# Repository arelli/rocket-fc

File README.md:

# rocket-fc

Open-source flight computer and ground station for model rockets, built on
the **Seeed XIAO ESP32-S3 + Wio-SX1262** (LoRa) kit.

The flight computer detects launch and apogee, fires the parachute ejection
charge, logs the flight to its own flash and sends live telemetry. A second
kit is the ground station: it receives the telemetry, serves the whole
control page over its own WiFi to a phone or laptop, and can be the launch
controller for the motor igniter.

> **Status:** version 0.1, bench-tested, not yet flown. Read
> [Safety](#safety) before building.

## Features

**Flight computer**
- Launch, burnout, apogee and landing detection (Kalman filter on barometer
  + accelerometer); single-shot ejection with lockout, confirmation and
  minimum altitude; optional deployment delay and backup timer.
- Layered pyro safety: hardware arm link, gate pull-down, software interlock
  until launch is detected, one shot per flight even across resets.
- Resumes a flight after an in-flight processor reset.
- Flight log in the XIAO's flash (4.8 MB, sessions kept after power-off) and
  PSRAM; no SD card needed.
- LoRa telemetry with CRC, duty-cycle limiter (EU 869 MHz by default) and
  event priority; attitude estimate; optional L76K GPS for recovery.
- LED and buzzer codes for every state, self-test faults and the landed
  altitude.

**Ground station**
- WiFi access point serving the UI: live gauges, attitude, plots, events,
  GPS recovery bearing, battery, both kits' settings and consoles, onboard
  log download. No app, no internet, no laptop needed.
- Launch controller: ARM switch, igniter continuity, countdown, abort.
- BENCH / FLIGHT mode switch the rocket follows; ping and signal-search mode;
  manual ejection by radio (optional, off by default).
- Every panel part (switches, button, buzzer, LEDs, battery) is optional.

**Software**
- Every tunable value is a setting: stored in flash, edited from the UI,
  identified by a CRC that is logged with the firmware commit.
- Decision logic is hardware-independent and unit-tested on the PC (17 test
  suites, including complete simulated flights).

## Hardware

| Kit | Parts |
|---|---|
| Flight computer | XIAO ESP32-S3 + Wio-SX1262, MPU-9250 IMU, BMP280 barometer, IRLB8748 pyro MOSFET, buzzer, LED, 18350 Li-ion cell, optional L76K GPS |
| Ground station | XIAO ESP32-S3 + Wio-SX1262, 18650 Li-ion cell (or a power bank), optional ARM / MODE switches, push button, launch MOSFET, buzzer, two LEDs |

| Flight computer | Ground station |
|---|---|
|  |  |

Full parts list, assembly and first-time setup:
**[docs/BUILD.md](docs/BUILD.md)**.

### PCBs

KiCad 10 boards for a home-made build (laser and etch), each part tagged on
the 3D render with what goes into each screw terminal and the resistor colour
codes.

**Flight computer** ([hardware/flight-pcb](hardware/flight-pcb/README.md)):

**Ground station** ([hardware/ground-pcb](hardware/ground-pcb/README.md)):

## Quick start

1. Build the two kits ([docs/BUILD.md](docs/BUILD.md)).
2. Install [VS Code](https://code.visualstudio.com/) with the **PlatformIO
   IDE** extension, clone this repository and open it.
3. Flash each kit over USB-C:
   ```
   pio run -e flight -t upload     # flight computer
   pio run -e ground -t upload     # ground station
   ```
4. Join the station's WiFi `rocketfc-XXXX` (password: `wifi` on its USB
   console the first time) and open **http://192.168.4.1**.
5. Set your own pairing key `rf_key`, press **Set upright**, and work
   through [docs/TESTING.md](docs/TESTING.md).

| PlatformIO env | Builds |
|---|---|
| `flight` | Flight computer firmware. One firmware for bench and flight: the test commands (simulated flight, test fire) need **bench mode**, which follows the ground station's MODE and ends at launch. |
| `ground` | Ground station firmware, with the UI embedded. |
| `native` | Unit tests on your computer: `pio test -e native` (needs a C++ compiler). |

## Safety

This project drives pyrotechnic charges and motor igniters.

- Run the whole bench procedure in [docs/TESTING.md](docs/TESTING.md) with a
  dummy load and bare nichrome **before fitting any charge**.
- Fit arm links and connect igniters last, at the pad, from the side.
- Read [docs/FLIGHT_LOGIC.md](docs/FLIGHT_LOGIC.md) to know exactly when the
  charge can fire.
- Set your own `rf_key` (the default is public) and keep the station's WiFi
  password private: anyone on that WiFi has the launch and ejection controls.
- Fly under your club's and your country's rules, including the radio rules
  for the band you use.

The software is provided as is, without warranty (see [LICENSE](LICENSE)).

## Documentation

| Document | Contents |
|---|---|
| [BUILD.md](docs/BUILD.md) | Parts, wiring, flashing, first-time setup, troubleshooting |
| [HARDWARE.md](docs/HARDWARE.md) | Pin maps, power, pyro and launch circuits, ground station panel, WiFi |
| [TESTING.md](docs/TESTING.md) | Unit tests, bench tests, pre-flight checklist |
| [FLIGHT_LOGIC.md](docs/FLIGHT_LOGIC.md) | States, deployment rules, interlocks, failure handling |
| [SETTINGS.md](docs/SETTINGS.md) | Every setting, how to change them, radio rules, bench mode |
| [INDICATORS.md](docs/INDICATORS.md) | LED patterns and buzzer codes |
| [TELEMETRY.md](docs/TELEMETRY.md) | Radio protocol, frame formats, CSV columns, logs |
| [ARCHITECTURE.md](docs/ARCHITECTURE.md) | Code structure, data flow, how to extend |

## Repository layout

```
include/        pin map (board_pins.h) and fixed constants
lib/fc_core/    hardware-independent logic, unit-tested on the PC
                (state machine, estimator, telemetry, settings, flash log, GPS,
                 launch control, remote-command codes, ...)
lib/fc_hal/     drivers: MPU-9250, BMP280, SX1262, GPS UART, flash, pyro, ADC, system
src/flight/     flight computer firmware (wiring of core + drivers)
src/ground/     ground station firmware and its WiFi server
test/           unit tests (pio test -e native)
tools/          ground_station.html (the UI), ground_station.py (USB recorder),
                pcb_export.py (KiCad checks and exports; with
                pcb_check.py, pcb_map.py, pcb_isolation.py, pcb_parts.py),
                schematics.py (ground station drawing), build scripts
hardware/       flight-pcb: KiCad 10 project of the flight computer
                (schematic = wiring master; routed board, laser files
                for a home-made build); ground-pcb: the ground station
                on a single-sided board
docs/           documentation and schematics
```

## Traceability

Every build is stamped with its git commit (`-dirty` if there were
uncommitted changes), printed at boot and logged as the first telemetry
event. The settings in use are identified by a CRC-32 (boot banner,
`status`, CONFIG event). Fly clean builds and keep the exported settings
file: a log then identifies exactly which code and configuration flew.

## Contributing

Bug reports, flight reports, hardware variants and code are welcome. See
[CONTRIBUTING.md](CONTRIBUTING.md) and the
[code of conduct](CODE_OF_CONDUCT.md). Changes are listed in
[CHANGELOG.md](CHANGELOG.md).

## License

[MIT](LICENSE).

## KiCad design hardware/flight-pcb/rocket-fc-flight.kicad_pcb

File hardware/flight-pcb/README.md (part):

# Flight computer PCB (KiCad 10)

KiCad project of the flight computer. The schematic is the **wiring master**:
pin numbers follow [include/board_pins.h](../../include/board_pins.h), and
[docs/HARDWARE.md](../../docs/HARDWARE.md) explains each circuit.

| File | Contents |
|---|---|
| `rocket-fc-flight.kicad_pro` | Project, design rules and net classes |
| `rocket-fc-flight.kicad_sch` | Schematic (one A3 sheet) |
| `rocket-fc-flight.kicad_pcb` | Board: 30 x 68 mm (75 mm with the mounting ears), two layers |
| `lib/rocket-fc.kicad_sym` | Symbols: XIAO ESP32-S3 + Wio-SX1262, SparkFun MPU-9250 breakout, 4-pin GY-BMP280, L76K |
| `lib/rocket-fc.pretty/` | Footprints of those modules, and the wire pads of J1 and J3 |
| `lib/rocket-fc.3dshapes/` | Simplified 3D models of those (boxes and cylinders, for the renders and the tube check by eye) |
| `out/` | Generated files (not committed) |

The library tables use `${KIPRJMOD}`, so the project opens on any computer
with no library setup.

**Status:** schematic done (ERC clean), board routed with a GND pour on
both faces: DRC 0 problems, schematic parity 0, `tools/pcb_check.py` ok.
Laser files ready (below); test etches of the raster method done, the
vector isolation method still to try. Since those etches: the cell, main
switch and arm link are soldered wires (no JST plug, one screw terminal
fewer) and the board is 6.6 mm shorter.

Routing uses both faces and **27 wire vias**: a hole with a short wire
soldered on both sides wherever a track changes face (no plated holes).

## Layout

The board sits centred in the 32 mm airframe, so the tall parts are on the
centre line and only low parts (resistors lying flat) are near the edges.
`y` runs from the XIAO's USB face (0) to the far end (68 mm).

| Zone (y, mm) | Top | Bottom |
|---|---|---|
| −7–0 | Two ears with M3 holes H1, H2; the notch between them is free for the USB-C plug | The cell and main switch wires (J1) leave through the same notch |
| 0–34 | XIAO with the Wio-SX1262 on top, USB-C flush with the notch; continuity divider (R4, R5, C3) on the left edge, battery divider (R1, R2, C2) on the right; BAT+ / BAT− wire pads | J1: four wire pads at y 9.5 (1 cell −, 2 cell +, 3–4 main switch); SparkFun MPU-9250 |
| 25–56 | Buzzer centred (34–46), gate resistors R6, R7 and the GPS lead pads J5 on the right edge | IRLB8748 (left) and 1 Ω 2 W resistor (right) lying flat (32–53); 470 µF standing between them (45–54) |
| 46–61 | 4-pin GY-BMP280, sensor side down, header at its far edge | |
| 56–59 | ARM link wire pads J3, one at each edge beside the barometer: CELL+ left, ARM right (seen from the top) | |
| 60–70 | | Screw terminal J4 (igniter), centred, pins at y 65 just past the barometer's joints; its wire entry overhangs the far end by 1.7 mm |
| 61–68 | M3 holes H3, H4 in the corners | |

- **USB:** the XIAO's USB-C face is at the board edge, in a 14 mm wide notch
  between the two ears, so the plug goes straight in with the board on its
  sled.
- **One connector:** the igniter's screw terminal J4, on the centre line
  (where the tube is tallest), wires entering from the far end. The cell,
  main switch and arm link are **soldered wires** (lighter than plugs and
  terminals, and they cannot shake loose): J1's four pads under the XIAO,
  J3's two pads at the edges beside the barometer. 0.5 mm² (20 AWG) stranded
  wire for J1 and J3 (they carry the firing current); tie or glue each lead
  to the board or sled next to its pad, so it does not flex at the joint.
- **No status LED** (the buzzer stays): see docs/HARDWARE.md.
- The L76K GNSS module is off the board, near the nose, on a 3-wire lead
  soldered to J5 (3V3, GND, TX); its symbol and footprint stay in the library.

| Footprint | Source |
|---|---|
| XIAO + Wio-SX1262 (U1) | XIAO pattern: 2 x 7, 2.54 mm pitch, rows 15.24 mm apart, 21 x 17.8 mm; **5V, D8, D9, D10 have no pad** (pull those pins out of the header strip before soldering it: the radio uses them through its own connector); two wire pads for the BAT pads on the XIAO underside, past the MPU |
| SparkFun MPU-9250 (U2) | SparkFun's Eagle board file, v10 (17.0 x 17.8 mm); chip side away from the board (its labelled side faces the PCB); **AD0, INT, AUXCL, AUXDA have no pad** (pull those pins); its standoff holes are not drilled (they would hit the XIAO pins) |
| GY-BMP280 4-pin (U3) | 10 x 13 mm, 2.54 mm header along a 10 mm edge. **Mounted sensor side down** (labels up, VIN in the square pad): with the sensor up, the real board's pin order (VIN GND SCL SDA) runs the other way to this footprint. The BMP280 then hangs about 1.5 mm above C1's joints |
| C1 470 µF 10 V | KiCad CP_Radial_D8.0mm_P3.50mm, standing on the bottom (12.5 mm tall at most) |
| Everything else | KiCad standard library: resistors lying flat (7.62 mm), 1 Ω 2 W (DIN0414, 15.24 mm), TO-220 lying flat, a 5.08 mm screw terminal (J4), 12 mm buzzer, solder-wire pads for the GPS lead. J1 and J3 are wire pads from `lib/rocket-fc.pretty/` (J1: the JST-XH 4-pin pad layout without the plug, 0.95 mm holes; J3: two separate 1.3 mm pads 20.8 mm apart). The two 100 nF discs sit at the board edge: **bend them flat** (3.5 mm high at most) |

## Parts

Every part tagged on the 3D render, what goes into each screw terminal
and wire pad (yellow tags), each part's value and what it is, and for the resistors the
colour code (4-band 5 %, 5-band 1 %; the render shows the 4-band one). Parts
on both faces: the bottom panel is seen from below. `python
tools/pcb_export.py board` redraws it (`tools/pcb_parts.py`, needs Pillow).

## Dimensions

Both faces straight on with the outline (30 x 68 mm, 75 mm with the ears;
ears 8 mm wide and 7 mm deep beside the 14 mm USB notch) and the M3 hole
positions (22.5 mm across, 67.75 mm along, 3.75 mm from the sides and the far
end, 3.5 mm from the ear tips) for the sled; the 27 wire vias ringed by net;
3D views of both faces. The same sheet with the parts list beside it:
[dims-parts.jpg](dims-parts.jpg):

`python tools/pcb_export.py board` redraws
both (`tools/pcb_dims.py`, needs Pillow).

## Making the board (laser and etch)

Both faces carry a **GND pour**: the copper between the tracks is kept and
tied to GND (0.7 mm from every other net, thermal spokes on GND pads), so
the laser only has to clear a band around each track and pad, and the etch
removes far less copper. Pieces of the pour that reach no GND pad stay as
floating copper (harmless). No pour under Q1's metal tab or the M3 screw
heads (keep-out areas; `tools/pcb_check.py` checks it); the laser files leave
the paint there, so a home-made board has unconnected copper islands under
them, touching no net. The tracks still
make every connection; the pour only adds to the GND ones.

**Ready to use:** [laser/](laser/) holds every file below for the current
board, and [rocket-fc-flight-laser.zip](laser/rocket-fc-flight-laser.zip)
all of them in one download. `python tools/pcb_export.py laser` writes them
to `out/laser/` and copies them there:

| File | Use |
|---|---|
| `…-top-isolation.nc`, `…-bottom-isolation.nc` | **Vector isolation G-code** (method A, below): outlines around all copper, the bottom mirrored |
| `…-top.svg`, `…-top-0.08mm.png` | Top copper as a raster image (method B), **negative**: black = laser fires (paint off, copper etched), white = copper stays. Only a 0.4 mm band round the copper is black, as in method A: areas without copper (the USB notch, under Q1's tab, round the M3 holes and the labels) stay white and end up as unconnected copper islands. Every hole centre is a small black dot, so the etch leaves a pit that centres the drill; the M3 holes and Q1's tab hole get a 0.6 mm black ring round that dot, so they are easy to find |
| `…-bottom.svg`, `…-bottom-0.08mm.png` | Bottom copper, the same, **mirrored** (as seen from below) |
| `…-jig.svg` | Registration jig: two 3 mm pin holes at the H1 and H4 positions |
| `….drl`, `…-drl_map.pdf`, `…-drill-report.txt` | Drill file (mm), drill map and hole count per size |
| `…-placement-map.png` | Where every part goes, both faces as lasered, with the 27 wire vias (red X) and the pins to solder on both faces (red ring, on the part's face): print it for assembly. Needs PyMuPDF (`pip install pymupdf`), like the PNGs |

Every file uses the same frame, the board outline's bounding box (30.0 x
75.0 mm), so they line up when placed at the same position:

- **LaserGRBL:** give every job the **same Offset X / Y** (e.g. 0, 0) and
  never move the bed or the jig between them. The G-code coordinates already
  start at the lower-left corner of that box (X 0–30, Y 0–75), so run it
  with the same origin as the jig. The PNGs come out 30.0 x 75.0 mm from
  their DPI (Autosize on): within half a line of the SVGs.
- **LightBurn:** one project, one layer each, align their centres; set the
  jig's outline to a layer that does not output.

### Method A: vector isolation (recommended, about 30 minutes a face)

`tools/pcb_isolation.py` turns KiCad's copper into outlines for the laser:
rings around all copper, starting half a spot from its edge, 20 % overlap,
until a 0.4 mm band is clear (where two rings meet in a narrow gap the gap
is already clear, and an outline never enters copper). Nothing else is
burned: areas without copper (the keep-outs under Q1's tab and the screw
heads, the gaps the pour leaves round the labels, the USB notch) stay painted
and become unconnected copper islands, harmless since they touch no net;
every hole centre gets a burned dot (the etched pit centres the drill), a
0.6 mm one at the M3 holes and Q1's tab hole; the board outline is traced as a cutting line. It then checks its own result: the copper left must contain all of
the design's copper, and no two nets may end up joined (a run that fails
exits with an error).

Open the `.nc` file in LaserGRBL (*File → Open*) and run it. The power is
M4 (dynamic): with GRBL's laser mode on (`$32=1`) the power drops in the
corners where the head slows down, so they do not over-burn. Settings, as
environment variables for `python tools/pcb_export.py laser`:

| Variable | Default | Meaning |
|---|---|---|
| `LASER_SPOT` | 0.1 | Burned line width (mm): measure a line on the test scrap |
| `LASER_BAND` | 0.4 | Width cleared around the copper (mm) |
| `LASER_FEED` | 300 | Speed (mm/min) |
| `LASER_S` | 980 | Power, of GRBL's `$30` maximum (1000 by default) |

### Method B: raster image (about 70 minutes a face)

The PNGs are for raster software such as LaserGRBL: pure black and white,
one pixel per line, 0.08 mm (12.5 lines/mm, stored in the file as 317.5
dpi). Lines narrower than the spot leave stripes of paint between them, so
the spacing is smaller than a diode laser's spot. Each face gets **two
passes without moving anything** in between:

1. **Horizontal:** load the PNG with **Passthrough** (engraves it exactly
   as it is, one line per pixel row; Autosize from the DPI).
2. **Vertical:** load the same PNG again with **Line To Line Tracing**,
   *Direction: Vertical*, *Quality* 12.5 lines/mm (the file's own
   resolution, so it is not resampled), same size and offset; check in the
   preview that it matches the image. It clears the paint left between the
   horizontal lines and cuts the vertical edges straight (one pass alone
   leaves a sawtooth on the edges across its lines).

Avoid **Vectorize**: it smooths the outlines and thins narrow tracks and pad
rings. For another line spacing set `LASER_LPMM` (lines per mm, e.g.
`LASER_LPMM=10 python tools/pcb_export.py laser` for 0.1 mm) and use the
same value as the vertical pass's Quality.

### Steps

1. **Blank:** double-sided FR4, 1.6 mm, at least 36 x 82 mm. Clean both
   faces (fine abrasive pad, then isopropyl alcohol) and spray thin coats of
   matte black paint on both. **Find the laser settings on a scrap** painted
   the same way first:
   - a power ladder at a fixed speed (e.g. 50, 65, 80, 98 % at 1000 mm/min);
     take the **lowest power that leaves bright copper**: more power burns
     past the edges and thins tracks and pad rings;
   - method A: measure the width of a single burned line and set
     `LASER_SPOT` to it (re-export), so the rings overlap properly;
   - method B: try both passes (horizontal, then vertical); if stripes of
     paint still stay between the lines, re-export with `LASER_LPMM=15`
     (0.067 mm);
   - LaserGRBL laser mode: M4 (dynamic) is better if GRBL's laser mode is on
     (`$32=1`); for the raster, M3 (constant power) also works, since every
     line ends in the margin outside the board.
2. **Top:** laser `top` onto the blank (method A: the `.nc` file; method B:
   both raster passes).
3. **Drill the four M3 holes** (3.2 mm) on their marks: they register the
   second face.
4. **Jig:** fix a sheet of cardboard or MDF to the bed and, without moving
   it afterwards, cut `jig` into it (a vector job: enough power and passes
   to cut through, at the same offset as the copper). Push two 3 mm pins
   into the holes (drill bits shank-down, or M3 screws from below),
   standing no higher than the board.
5. **Bottom:** flip the board **left to right** (about its long axis) onto
   the pins: H2 and H3 now sit on them. Laser `bottom` at the same position
   as the jig.
6. **Etch** both faces (ferric chloride or sodium persulfate), strip the
   paint with acetone. **TOP and BOT must read correctly** on their faces; if
   BOT is mirror-writing, the bottom was not mirrored. Check every track for
   breaks and shorts with a meter before drilling (also each track against
   the GND pour next to it).
7. **Drill** from the etched pits, then cut and file to the outline (the
   thin copper line on each face). Bits:

| Bit | Holes |
|---|---|
| 0.8 mm | 27 wire vias, resistors, 100 nF, C1, GPS lead pads (J5) |
| 1.0 mm | XIAO, MPU-9250 and barometer headers, BAT pads, buzzer, J1 wire pads |
| 1.2 mm | IRLB8748 (Q1) leads, 1 Ω 2 W (R3) |
| 1.3 mm | ARM link wire pads J3, screw terminal J4 |
| 3.2 mm | M3 holes H1–H4 (step 3) |
| 3.5 mm | Q1's tab hole (a 3.2 mm hole also takes the M3 screw) |

## Assembly order

No plated holes: a part is soldered on the face opposite to it, and some
joints end up under a part. `tools/pcb_check.py` lists them, and the
placement map ([laser/rocket-fc-flight-placement-map.png](laser/rocket-fc-flight-placement-map.png)) shows where each part goes,
the wire vias and the both-face pins; in practice:

0. **All 27 wire vias first**: a bare wire (e.g. a resistor lead offcut)
   through each 0.8 mm via hole, soldered on both faces and trimmed flush.
   Several sit under parts (the XIAO, MPU, buzzer, barometer, J4, R3, R4,
   R7).
1. Small parts in the edge strips, then Q1, R3 and C1 (bottom). **Trim C1's
   joints flush** on the top and put Kapton tape over them: the barometer's
   sensor hangs over them.
2. The J1 wires (cell −, cell +, main switch, main switch): in from the
   bottom, soldered on top and **trimmed flush**, under where the XIAO goes.
   Strip about 3 mm, so no bare wire shows on the bottom.
3. The XIAO's header strips (top, **low male headers, not sockets**: the
   stack must stay under 11.9 mm; 5V, D8, D9, D10 pulled), soldered on the
   bottom and **trimmed flush**: the MPU board sits over these joints.
   The strips go on without the XIAO (it is soldered onto them in step 5),
   so a XIAO that already has header pins must lose them first.
4. The MPU-9250 on its headers (bottom), soldered on the top between the
   XIAO header strips.
5. The XIAO with the Wio-SX1262 onto its header strips, soldered from above,
   and the two wires from the XIAO's BAT pads to BAT+ / BAT− (past the MPU,
   both faces free).
6. The buzzer (top), soldered on the bottom; then the barometer (top),
   **sensor side down**, labels up, VIN in the square pad.
7. The igniter terminal J4 (bottom; its two wire vias, IGN+ and GND, are
   under it: soldered and trimmed in step 0), the arm link wires (J3, in from the
   top, soldered on the bottom) and the GPS lead.

Pins that `tools/pcb_check.py` lists under "solder on both faces" carry
copper on both sides and need a joint on each.

## Ordering from a PCB maker

The same board can be ordered from a PCB maker instead of etched at home.
**Ready to upload:** [fab/rocket-fc-flight-fab.zip](fab/rocket-fc-flight-fab.zip).
`python tools/pcb_export.py fab` writes `out/fab/` and copies the zip there:

| File | Use |
|---|---|
| `rocket-fc-flight-fab.zip` | **Upload this.** Gerbers (Protel extensions: `.gtl`/`.gbl` copper, `.gts`/`.gbs` mask, `.gto`/`.gbo` silkscreen, `.gm1` outline), Excellon drill files in mm (`-PTH.drl` plated, `-NPTH.drl` unplated), Gerber job file |
| `gerbers/` | The same files unzipped, to open in KiCad's Gerber Viewer |
| `…-drill-report.txt` | Hole sizes and counts: plated 0.8–1.3 mm (86), unplated 3.2 mm (M3 holes) and 3.5 mm (Q1's tab) |

Only copper, mask, silkscreen and the outline go in; the laser jig
(`User.1`), the fab, courtyard and comment layers stay out. Check the
maker's preview after uploading: outline with the USB notch, the four M3
holes and Q1's tab hole unplated, TOP / BOT readable on their faces.

Order settings (enter them on the maker's page):

| Setting | Value |
|---|---|
| Layers | 2 |
| Size | 30 x 75 mm (read from the outline) |
| Material, thickness | FR4, 1.6 mm |
| Copper | 1 oz (35 µm) outside |
| Surface finish | lead-free HASL (ENIG works too, at more cost) |
| Solder mask, silkscreen | green, white (any colour works) |
| Vias | tented (as designed; an untented via just gets a tinned ring) |
| Quantity | 3 at Aisler (sold in sets of 3), 5 at JLCPCB / PCBWay (their minimum) |
| Everything else | default: one design, single board (no panel), no castellated holes, gold fingers or edge plating; at JLCPCB "Remove Mark" if wanted |

The GND pour stays on a made board too (it is normal there, and helps the
radio's ground). A made board has **plated holes**, which changes the
assembly:

- Every hole joins the two faces, so each pin is soldered once, on the face
  opposite its part, and the 27 wire vias are ordinary vias: **no wires**,
  skip step 0 of the assembly order.
- The order of the parts above still holds where they stack (C1 before the
  barometer, the J1 wires and the XIAO header strips before the MPU, joints under a
  module trimmed flush, Kapton over C1's joints).
- `tools/pcb_check.py` and the "solder on both faces" list are for the
  home-made board only.

Checked against the makers' rules (DRC with the silkscreen and mask rules
switched on, on a copy of the project): no mask bridges; 24 silkscreen
warnings, all cosmetic (silkscreen over pads is cut away by the maker, three
reference labels and part of J4's outline touch the board edge). Silkscreen
text is 1.0 mm (BAT+ / BAT− 0.8 mm, below JLCPCB's 1.0 mm minimum: may print
blurred) and lines 0.12 mm (thickened or faint below the usual 0.15 mm).
The USB notch's inner corners come out rounded by the router bit (about
0.5–1 mm radius); the USB-C plug and J1's wires stay clear of them. The
0.8 mm vias are too large to tent reliably: the mask may sink into the hole,
which does no harm.

## Checks

`python tools/pcb_export.py` (from the repository root) runs:

- **ERC** on the schematic.
- **DRC** with schematic parity. Silkscreen and solder-mask rules are off
  (home-made board: neither). Holes inside another part's courtyard are
  allowed: that is how the board fits, and the next check covers it.
  Floating pieces of the GND pour ("isolated copper") are allowed, and a GND
  pad may join the pour with a single thermal spoke (each has its track).
- **`tools/pcb_check.py`** (with KiCad's Python), the rules of a board without
  plated holes:
  - every through-hole joint can be soldered (on the face opposite its part,
    or on its own face when the pin is exposed there, e.g. a lying resistor);
    joints under a module give the assembly order above;
  - every track meets a pin only on a face where that pin is soldered, and
    wire vias sit where both faces are reachable;
  - no foreign copper (tracks, vias or the GND pour) under the IRLB8748's
    metal tab (it is the drain) or under the M3 screw heads;
  - every part fits the tube: 15.5 mm radius, its height (table in the
    script) at its distance from the centre line.

Measure before etching (the heights in `tools/pcb_check.py` are estimates):

| Part | Assumed | Limit where it sits |
|---|---|---|
| XIAO + Wio-SX1262 stack on its headers | 10.0 mm | 11.9 mm |
| Screw terminal J4 | 10.0 mm | 13.8 mm |
| Buzzer | 9.5 mm | 13.5 mm |
| C1 470 µF standing (bottom) | 12.5 mm | 13.9 mm |

## Board constraints

- Airframe inner diameter 32 mm: board centred, 30 mm wide; four M3 holes
  for the sled (two ears at the USB end, two corners at the far end).
- Off the board, on soldered wires: 18350 cell and main switch (J1), arm
  link (J3), GPS module (J5). The igniter on the screw terminal J4 (changed
  often in testing).
- Made at home: laser-exposed resist and etching, two layers, no plated holes.
  Through-hole parts only (their leads also join the two sides).
  Design rules (project settings): tracks ≥ 0.4 mm, clearance 0.3 mm,
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
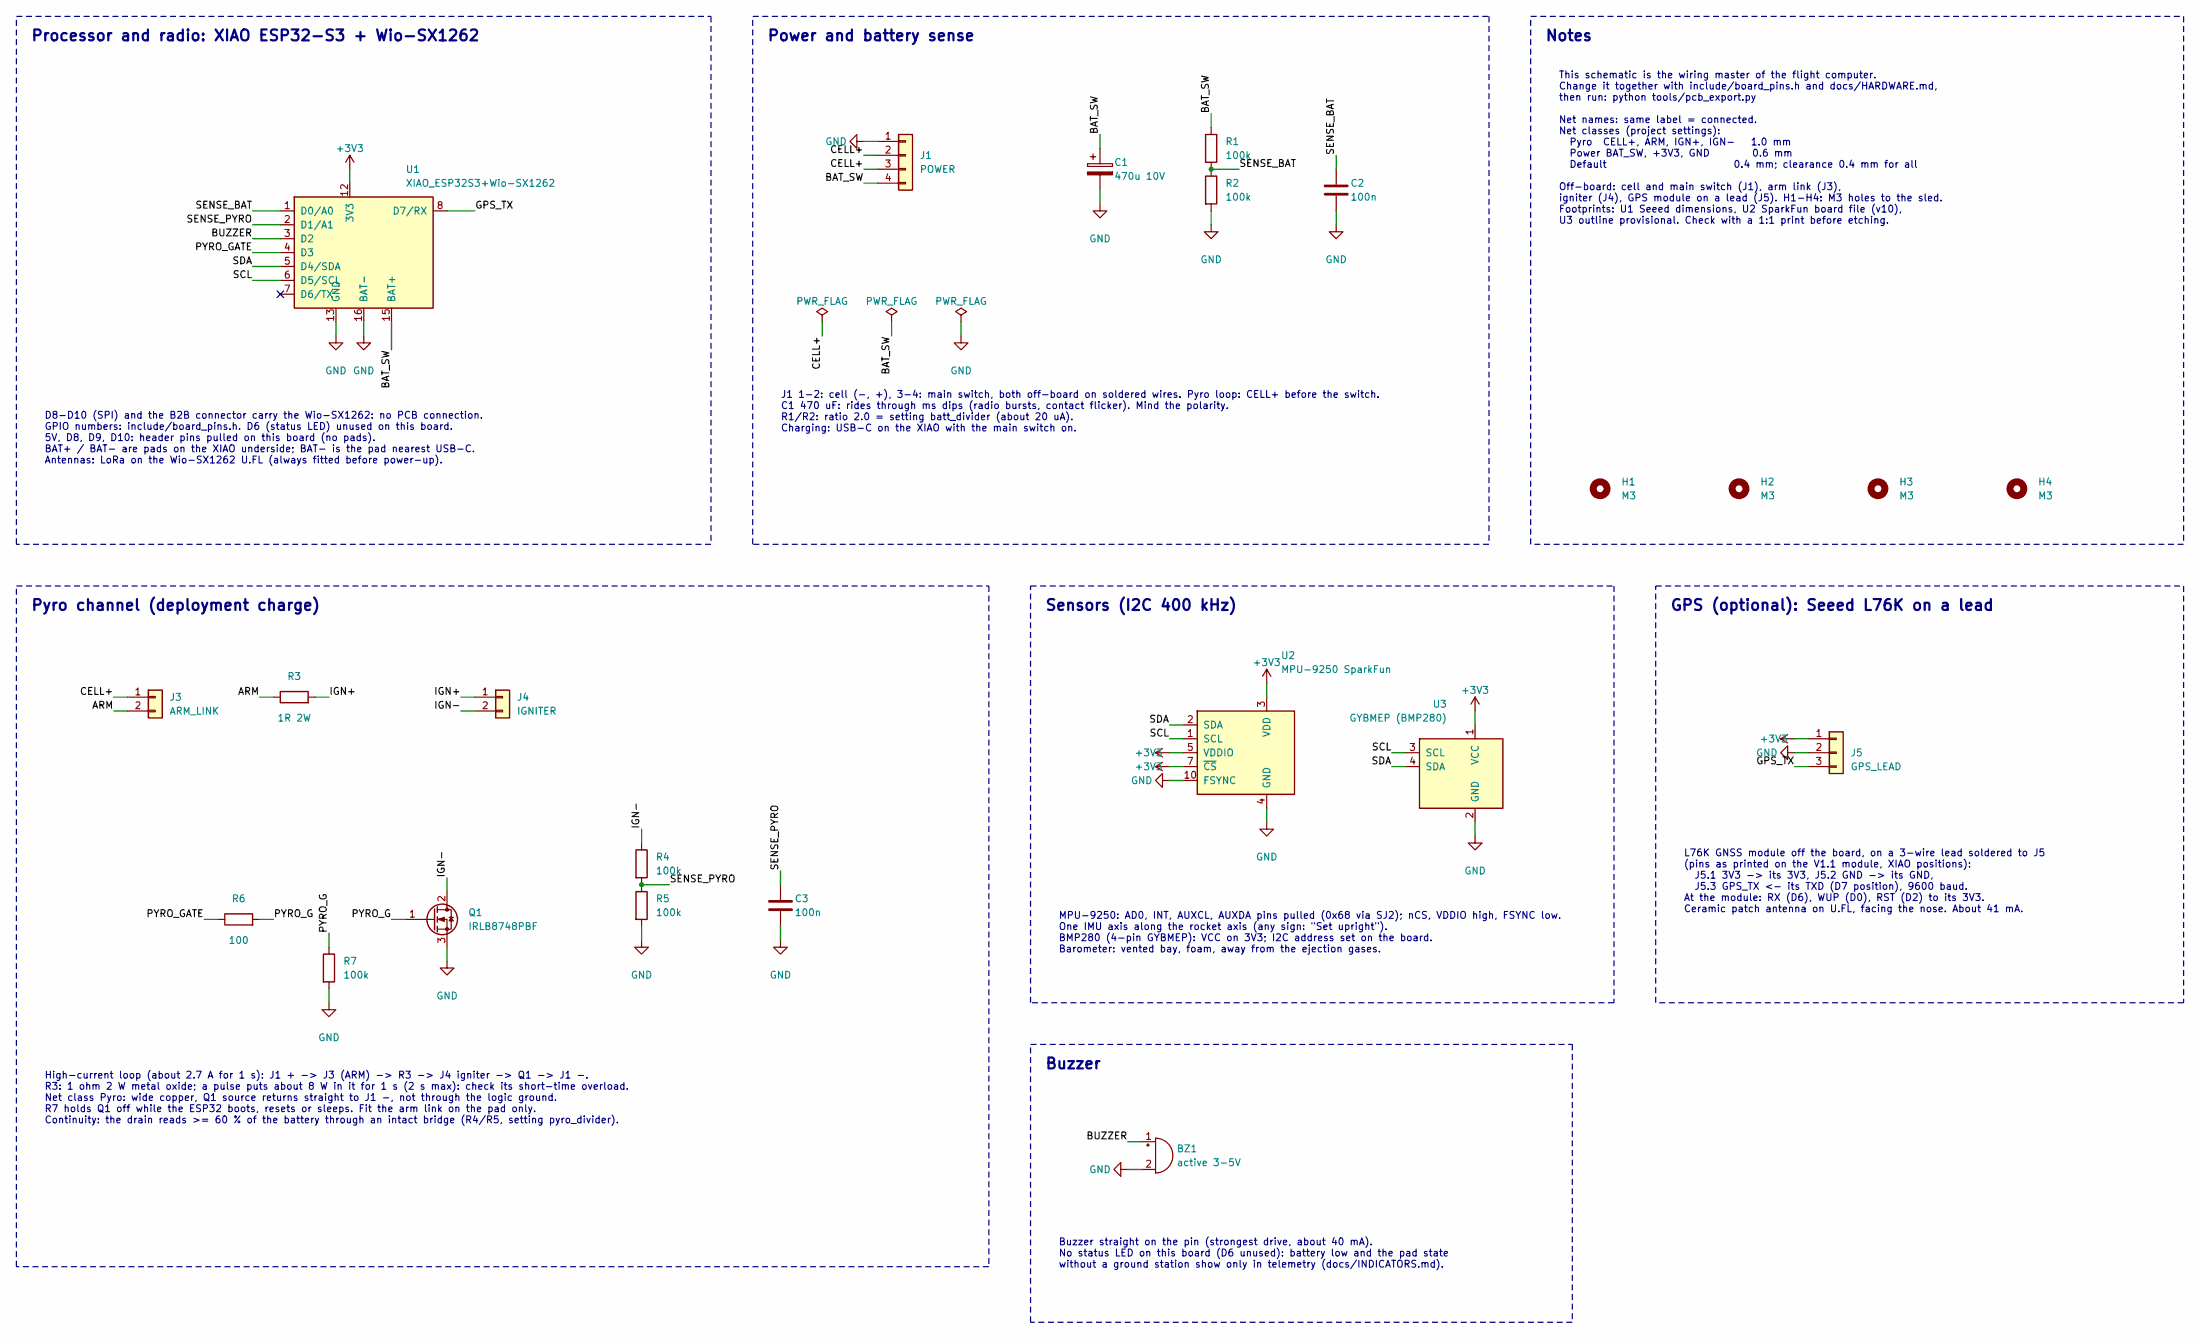
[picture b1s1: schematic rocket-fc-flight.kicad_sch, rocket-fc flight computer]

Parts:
BZ1: active 3-5V; Buzzer_12x9.5RM7.6
C1: 470u 10V; CP_Radial_D8.0mm_P3.50mm
C2, C3: 100n; C_Disc_D3.0mm_W1.6mm_P2.50mm
H1, H2, H3, H4: M3; MountingHole_3.2mm_M3
J1: POWER; SolderWire_1x04_P2.50mm_D0.95mm
J3: ARM_LINK; WirePads_1x02_P20.80mm_D1.3mm
J4: IGNITER; TerminalBlock_Phoenix_MKDS-1,5-2-5.08_1x02_P5.08mm_Horizont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
J5: GPS_LEAD; SolderWire-0.25sqmm_1x03_P4.2mm_D0.65mm_OD1.7mm
Q1: IRLB8748PBF; TO-220-3_Horizontal_TabDown
R1, R2, R4, R5, R7: 100k; R_Axial_DIN0207_L6.3mm_D2.5mm_P7.62mm_Horizontal
R3: 1R 2W; R_Axial_DIN0414_L11.9mm_D4.5mm_P15.24mm_Horizontal
R6: 100; R_Axial_DIN0207_L6.3mm_D2.5mm_P7.62mm_Horizontal
U1: XIAO_ESP32S3+Wio-SX1262; XIAO_ESP32S3_Wio-SX1262_THT
U2: MPU-9250 SparkFun; SparkFun_MPU-9250_Breakout_v10
U3: GYBMEP (BMP280); GY-BMP280_4pin_P2.54mm

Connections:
+3V3: J5.1, U1.12 (3V3), U2.3 (VDD), U2.5 (VDDIO), U2.7 (~CS), U3.1 (VCC)
/ARM: J3.2, R3.1
/BAT_SW: C1.1, J1.4, R1.1, U1.15 (BAT+)
/BUZZER: BZ1.1 (+), U1.3 (D2)
/CELL+: J1.2, J1.3, J3.1
/GPS_TX: J5.3, U1.8 (D7/RX)
/IGN+: J4.1, R3.2
/IGN-: J4.2, Q1.2 (D), R4.1
/PYRO_G: Q1.1 (G), R6.2, R7.1
/PYRO_GATE: R6.1, U1.4 (D3)
/SCL: U1.6 (D5/SCL), U2.1 (SCL), U3.3 (SCL)
/SDA: U1.5 (D4/SDA), U2.2 (SDA), U3.4 (SDA)
/SENSE_BAT: C2.1, R1.2, R2.1, U1.1 (D0/A0)
/SENSE_PYRO: C3.1, R4.2, R5.1, U1.2 (D1/A1)
GND: BZ1.2 (-), C1.2, C2.2, C3.2, J1.1, J5.2, Q1.3 (S), R2.2, R5.2, R7.2, U1.13 (GND), U1.16 (BAT-), U2.4 (GND), U2.10 (FSYNC), U3.2 (GND)

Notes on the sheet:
Processor and radio: XIAO ESP32-S3 + Wio-SX1262
D8-D10 (SPI) and the B2B connector carry the Wio-SX1262: no PCB connection. GPIO numbers: include/board_pins.h. D6 (status LED) unused on this board. 5V, D8, D9, D10: header pins pulled on this board (no pads). BAT+ / BAT- are pads on the XIAO underside; BAT- is the pad nearest USB-C. Antennas: LoR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
Power and battery sense
J1 1-2: cell (-, +), 3-4: main switch, both off-board on soldered wires. Pyro loop: CELL+ before the switch. C1 470 uF: rides through ms dips (radio bursts, contact flicker). Mind the polarity. R1/R2: ratio 2.0 = setting batt_divider (about 20 uA). Charging: USB-C on the XIAO with the main switch o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
Pyro channel (deployment charge)
High-current loop (about 2.7 A for 1 s): J1 + -> J3 (ARM) -> R3 -> J4 igniter -> Q1 -> J1 -. R3: 1 ohm 2 W metal oxide; a pulse puts about 8 W in it for 1 s (2 s max): check its short-time overload. Net class Pyro: wide copper, Q1 source returns straight to J1 -, not through the logic ground. R7 ho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
Sensors (I2C 400 kHz)
MPU-9250: AD0, INT, AUXCL, AUXDA pins pulled (0x68 via SJ2); nCS, VDDIO high, FSYNC low. One IMU axis along the rocket axis (any sign: "Set upright"). BMP280 (4-pin GYBMEP): VCC on 3V3; I2C address set on the board. Barometer: vented bay, foam, away from the ejection gases.
GPS (optional): Seeed L76K on a lead
L76K GNSS module off the board, on a 3-wire lead soldered to J5 (pins as printed on the V1.1 module, XIAO positions): J5.1 3V3 -> its 3V3, J5.2 GND -> its GND, J5.3 GPS_TX <- its TXD (D7 position), 9600 baud. At the module: RX (D6), WUP (D0), RST (D2) to its 3V3. Ceramic patch antenna on U.FL, faci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
Buzzer
Buzzer straight on the pin (strongest drive, about 40 mA). No status LED on this board (D6 unused): battery low and the pad state without a ground station show only in telemetry (docs/INDICATORS.md).
Notes
This schematic is the wiring master of the flight computer. Change it together with include/board_pins.h and docs/HARDWARE.md, then run: python tools/pcb_export.py Net names: same label = connected. Net classes (project settings): Pyro CELL+, ARM, IGN+, IGN- 1.0 mm Power BAT_SW, +3V3, GND 0.6 mm De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

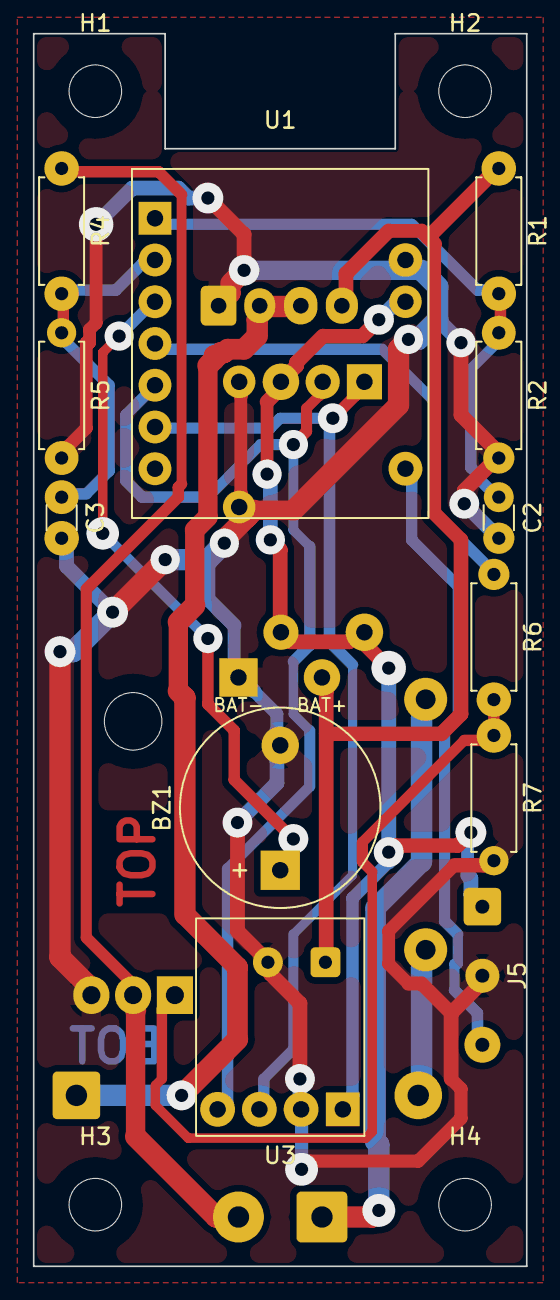
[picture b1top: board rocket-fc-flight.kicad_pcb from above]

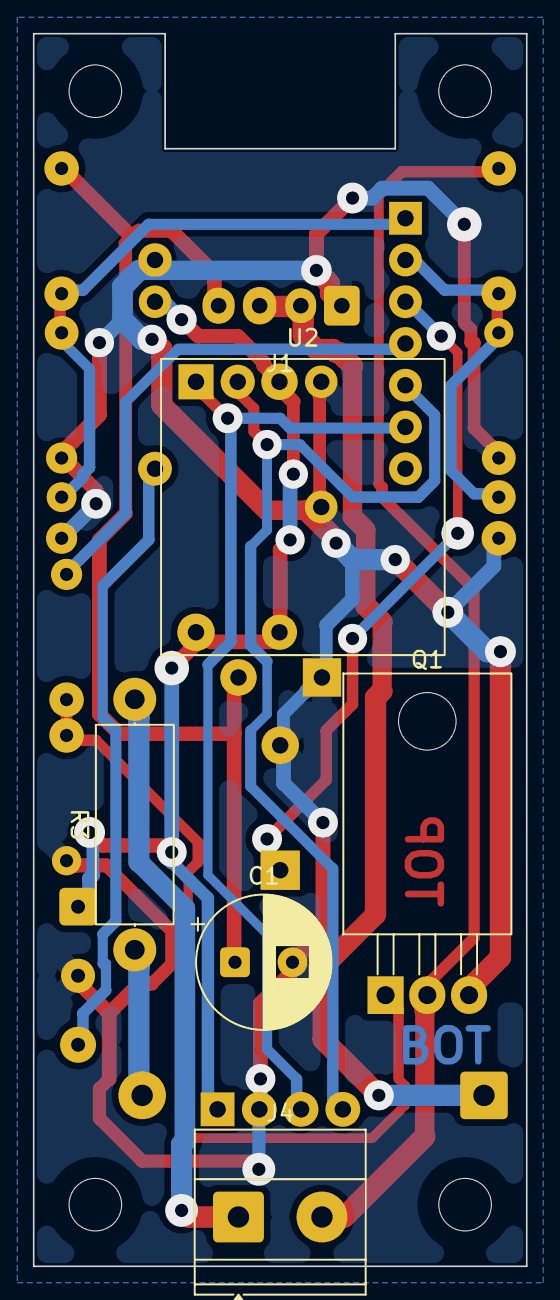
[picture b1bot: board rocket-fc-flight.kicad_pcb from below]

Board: 2 copper layers, 30.0 x 75.0 mm, 23 parts (6 on the bottom side), 15 nets.

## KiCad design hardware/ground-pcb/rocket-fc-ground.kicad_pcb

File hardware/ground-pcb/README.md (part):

# Ground station PCB (KiCad 10)

KiCad project of the ground station (second XIAO ESP32-S3 + Wio-SX1262 kit,
launch controller). The schematic is the wiring master of this board: pin
numbers follow `pins::ground` in
[include/board_pins.h](../../include/board_pins.h), and
[docs/HARDWARE.md](../../docs/HARDWARE.md#ground-station-second-kit)
explains each circuit. The hand-wired station drawn by `tools/schematics.py`
is the same circuit.

| File | Contents |
|---|---|
| `rocket-fc-ground.kicad_pro` | Project, design rules and net classes |
| `rocket-fc-ground.kicad_sch` | Schematic (one A3 sheet) |
| `rocket-fc-ground.kicad_pcb` | Board: 100 x 80 mm, all tracks on the bottom face |
| `lib/rocket-fc.kicad_sym` | Symbol: XIAO ESP32-S3 + Wio-SX1262 on female headers (all 14 pins) |
| `lib/rocket-fc.pretty/` | Its footprint |
| `lib/rocket-fc.3dshapes/` | Simplified 3D model of the kit (the flight board's, raised onto the sockets) |
| `out/` | Generated files (not committed) |

The library tables use `${KIPRJMOD}`, so the project opens on any computer
with no library setup.

**Status:** schematic done (ERC clean), board routed on one face with a
GND pour: DRC 0 problems, schematic parity 0, `tools/pcb_check.py` ok.
Laser and order files ready (below). Not built yet.

**Single-sided, no wire vias.** All the copper (tracks and a GND pour) is on
the bottom face; every part sits on the bare top face and is soldered
underneath. Use a single-sided blank: one laser job, no flipping, no
registration jig.

## Layout

`y` runs from the USB edge (0) to the terminal edge (80 mm), `x` from left to
right seen from the top.

| Zone | Parts |
|---|---|
| Top edge, centre | XIAO + Wio-SX1262 (U1) on two 1x7 female headers, USB-C 1 mm in from the edge |
| Top left | Buzzer BZ1, button connector J6, ON LED (LED1, R9) |
| Left edge | Launch divider R4, R5, ARM bypass R8; gate resistors R6, R7; IRLB8748 (Q1) standing |
| Under U1 | XIAO BAT lead connector J5, battery divider R1, R2, LINK LED (LED2, R10) |
| Right | MODE switch connector J7, 1000 uF capacitor C1; the rest is free room |
| Bottom | 1 ohm 5 W resistor R3 lying flat; screw terminals J1 igniter, J2 18650, J3 ARM switch, wires entering from the bottom edge |
| Corners | M3 holes H1-H4 (4 mm in from each edge) |

### Connectors

| Ref | Part | Pins (left to right, seen from the top) | Goes to |
|---|---|---|---|
| J1 | Screw terminal 5.08 mm | IGN+, IGN- | Launch leads (the docs' J1/J2), igniter |
| J2 | Screw terminal 5.08 mm | **-**, **+** | 18650 cell holder |
| J3 | Screw terminal 5.08 mm | CELL+, ARM | ARM switch SW2 (rated 5 A or more) |
| J4 | JST-XH 2, vertical | CELL+, BAT_SW | Power switch SW1 |
| J5 | JST-XH 2, vertical | **BAT-**, **BAT+** | The XIAO's BAT pads (underside), short lead |
| J6 | JST-XH 2, vertical | BUTTON, GND | Push button S1 |
| J7 | JST-XH 2, vertical | MODE, GND | MODE switch SW3 (open = BENCH) |

- **CELL+ is live** whenever a cell is in J2: J3 and J4 carry the cell
  voltage before their switches (the launch channel bypasses the power
  switch, as in the hand-wired station).
- The launch current runs CELL+ (J2) -> J3 -> ARM switch -> R3 -> J1 ->
  igniter -> J1 -> Q1 -> GND track straight back to J2, on 2 mm tracks.
- The panel parts (switches, button) stay off the board, in the box lid,
  on JST-XH leads; the LEDs and buzzer are on the board (see *Assembly*
  for LEDs in the lid instead).
- J5: the XIAO's BAT pads are on its underside, so they cannot reach the
  female headers. Solder a short two-wire lead to them, crimp a JST-XH
  plug on it and plug it into J5. This keeps the XIAO removable.

| Footprint | Source |
|---|---|
| XIAO + Wio-SX1262 (U1) | `lib/`: XIAO pattern, 2 x 7, 2.54 mm pitch, rows 15.24 mm apart, all 14 pads (the female headers need them; 3V3, 5V, D8-D10 are unconnected); oval 2.6 x 1.9 mm pads; pin names on the silkscreen |
| Everything else | KiCad standard library: resistors lying flat on a 10.16 mm pitch, 5 W cement resistor (25 x 9 mm, 27.94 mm), TO-220 standing, 1000 uF 10 mm radial (5 mm), 5 mm LEDs, 12 mm buzzer (7.6 mm), JST-XH vertical, Phoenix MKDS 5.08 mm terminals, M3 holes |

Pads are enlarged on the board itself for the laser (resistors 2.4 mm,
terminals 3.2 mm, R3 3.0 mm, C1 and the buzzer 2.8 mm, Q1 2.1 x 3.4 mm,
JST 2.0 x 2.8 mm, LEDs 2.0 x 2.6 mm), so they differ from the library
footprints (that DRC check is off): **Update Footprints from Library** would
shrink them back.

## Parts

Every part tagged on the 3D render, what goes into each screw terminal
(yellow tags), each part's value and what it is, and for the resistors the
colour code (4-band 5 %, 5-band 1 %; the render shows the 4-band one). Every
part sits on the top face. `python tools/pcb_export.py --board ground board`
redraws it (`tools/pcb_parts.py`, needs Pillow).

## Dimensions

Both faces straight on with the outline (100 x 80 mm) and the M3 hole
positions (92 x 72 mm apart, 4 mm from the edges), and 3D views of both
faces. The same sheet with the parts list beside it:
[dims-parts.jpg](dims-parts.jpg):

`python tools/pcb_export.py --board ground board` redraws both (`tools/pcb_dims.py`, needs Pillow).

## Making the board (laser and etch)

Same method as the flight board ([hardware/flight-pcb](../flight-pcb/README.md#making-the-board-laser-and-etch)),
for one face. The GND pour fills the copper between the tracks (0.7 mm from
every other net), so the laser only clears a band round each track and pad.

**Ready to use:** [laser/](laser/) holds every file below for the current
board, and [rocket-fc-ground-laser.zip](laser/rocket-fc-ground-laser.zip)
all of them in one download. `python tools/pcb_export.py --board ground
laser` writes them to `out/laser/` and copies them there:

| File | Use |
|---|---|
| `…-bottom-isolation.nc` | **Vector isolation G-code** (method A, about 56 min): outlines round all copper, mirrored |
| `…-bottom.svg`, `…-bottom-0.08mm.png` | The copper as a raster image (method B), **negative** (black = laser fires, white = copper stays), mirrored. Only a 0.4 mm band round the copper is black: areas without copper (round the M3 holes and the labels) stay white, as unconnected copper islands. Every hole centre is a small black dot (the etched pit centres the drill); the M3 holes get a 0.6 mm black ring round it |
| `….drl`, `…-drl_map.pdf`, `…-drill-report.txt` | Drill file (mm), drill map and hole count per size |
| `…-placement-map.png` | Where every part goes (top face, with the copper seen through the board) and the copper face as lasered: print it for assembly |

The frame of every file is the board outline (100 x 80 mm). The copper
labels are 2.5-3 mm high with a 0.5-0.6 mm stroke, so they survive the
laser and the etch.

### Method A: vector isolation (recommended, about 56 minutes)

Open the `.nc` file in LaserGRBL (*File → Open*) and run it: it starts at
the board's lower-left corner (X 0-100, Y 0-80), M4 power with `$32=1`.
Settings (`LASER_SPOT`, `LASER_BAND`, `LASER_FEED`, `LASER_S`) as for the
[flight board](../flight-pcb/README.md#method-a-vector-isolation-recommended-about-30-minutes-a-face).

### Method B: raster image

The PNG is 0.08 mm a pixel (12.5 lines/mm, 317.5 dpi: Autosize gives
100 x 80 mm). Two passes **without moving anything** in between:

1. **Horizontal:** the PNG with **Passthrough**.
2. **Vertical:** the same PNG with **Line To Line Tracing**, *Direction:
   Vertical*, *Quality* 12.5 lines/mm, same size and offset.

Avoid Vectorize. Details: [flight board](../flight-pcb/README.md#method-b-raster-image-about-70-minutes-a-face).

The files are **mirrored** because they show the copper face as seen from
below, which is how it lies on the laser bed (copper up). **BOT** and the
connector labels in the copper read correctly on the finished board.

### Steps

1. **Blank:** single-sided FR4, 1.6 mm, at least 106 x 86 mm. Clean the
   copper (fine abrasive pad, then isopropyl alcohol) and spray thin coats of
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
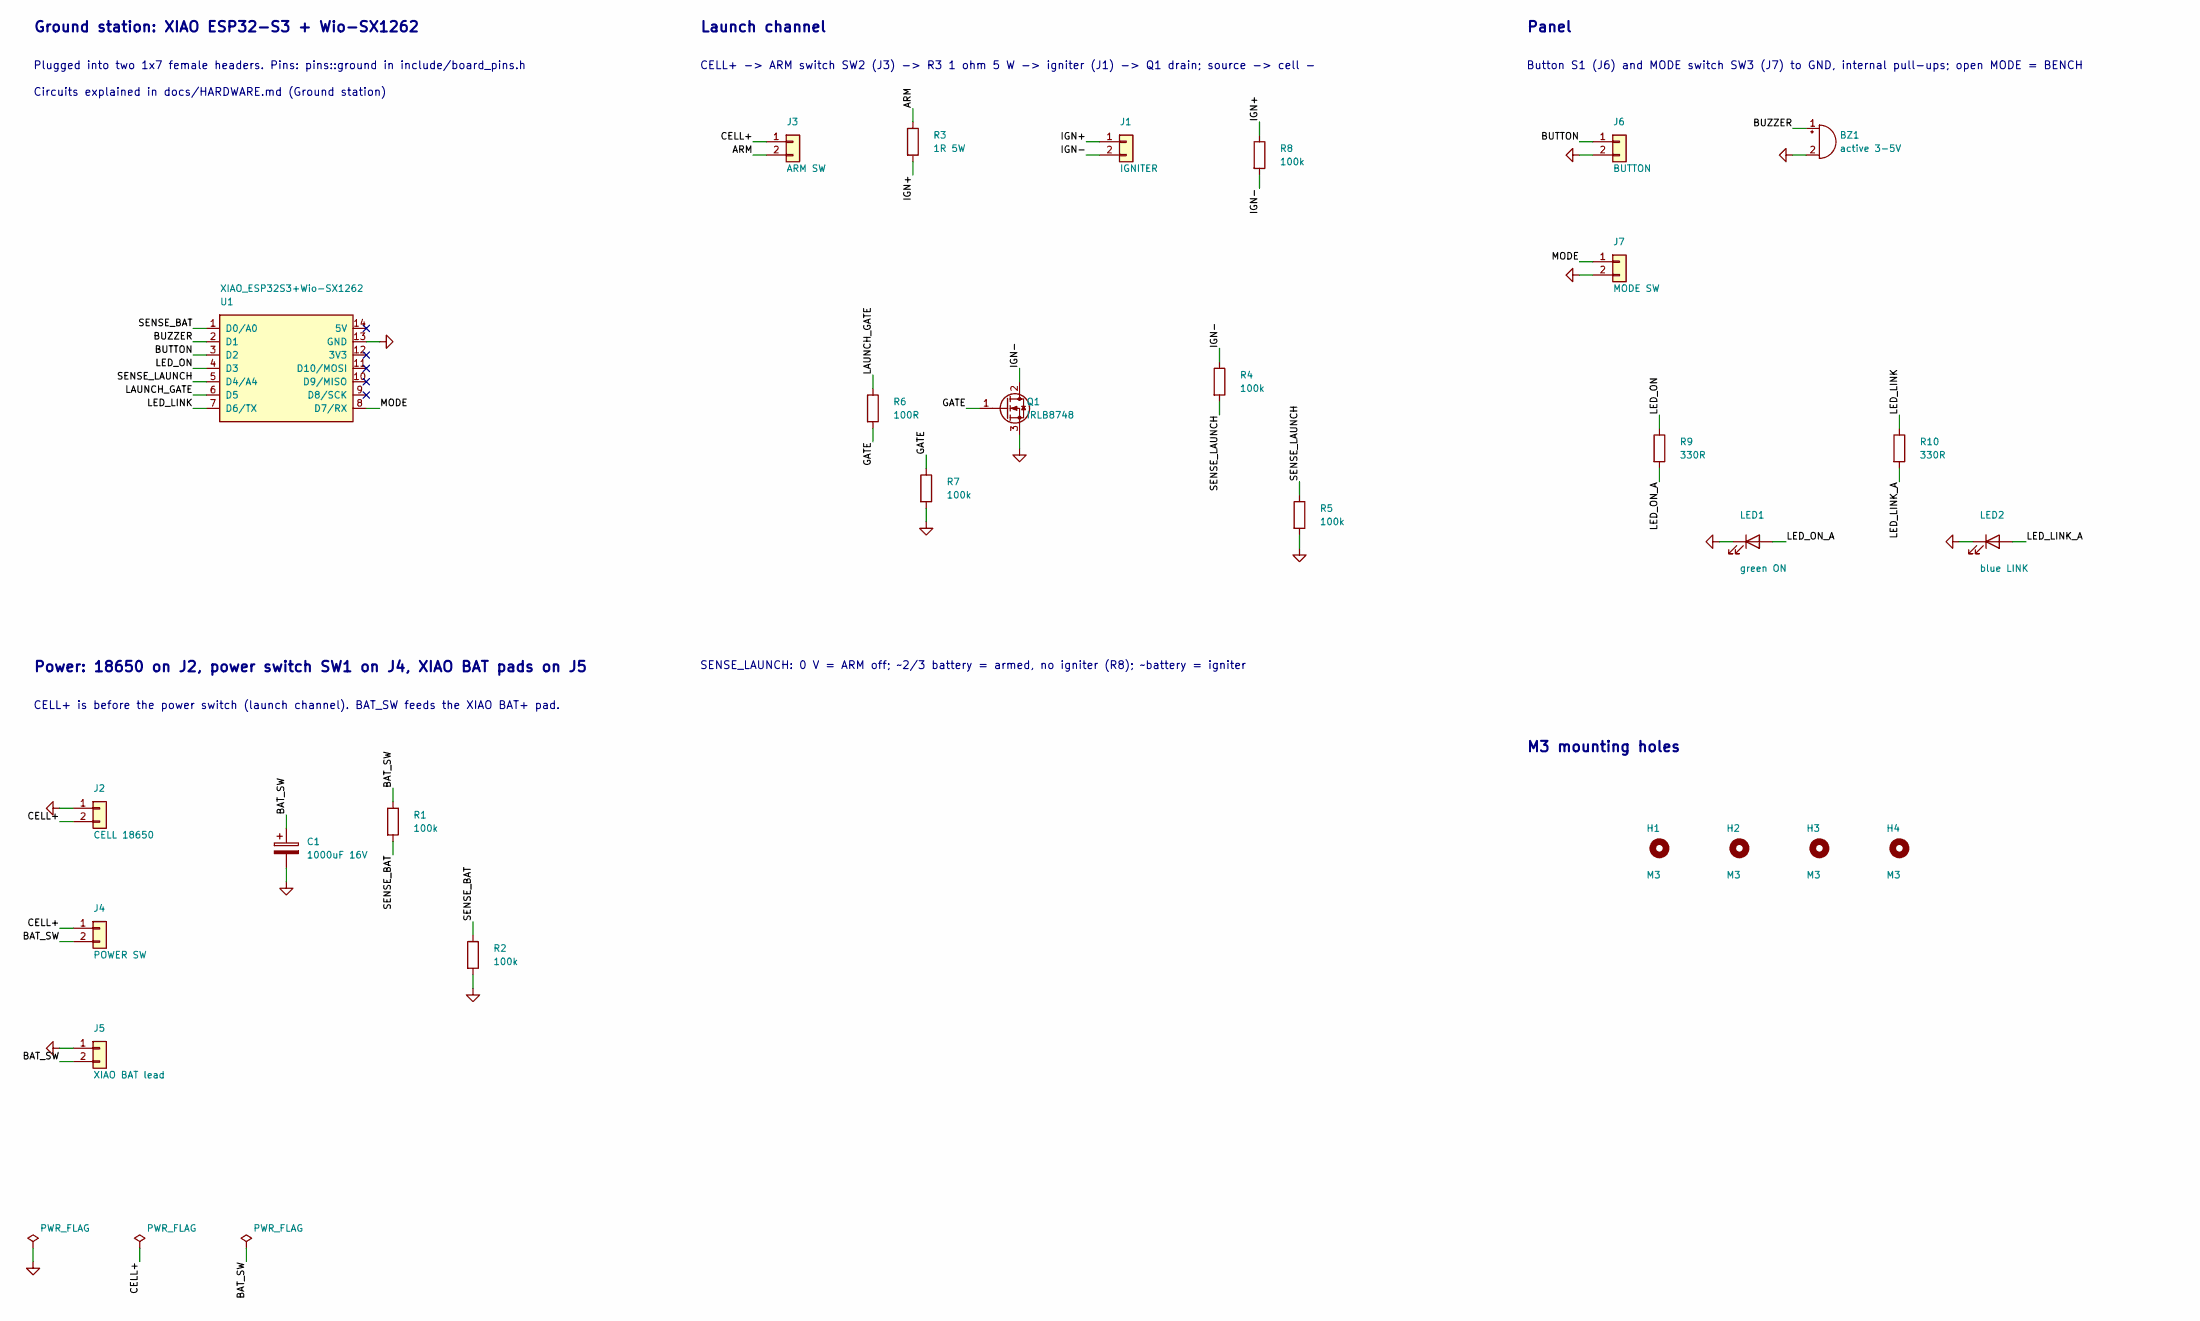
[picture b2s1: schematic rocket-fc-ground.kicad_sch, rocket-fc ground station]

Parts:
BZ1: active 3-5V; Buzzer_12x9.5RM7.6
C1: 1000uF 16V; CP_Radial_D10.0mm_P5.00mm
H1, H2, H3, H4: M3; MountingHole_3.2mm_M3
J1: IGNITER; TerminalBlock_Phoenix_MKDS-1,5-2-5.08_1x02_P5.08mm_Horizont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
J2: CELL 18650; TerminalBlock_Phoenix_MKDS-1,5-2-5.08_1x02_P5.08mm_Horizont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
J3: ARM SW; TerminalBlock_Phoenix_MKDS-1,5-2-5.08_1x02_P5.08mm_Horizont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
J4: POWER SW; JST_XH_B2B-XH-A_1x02_P2.50mm_Vertical
J5: XIAO BAT lead; JST_XH_B2B-XH-A_1x02_P2.50mm_Vertical
J6: BUTTON; JST_XH_B2B-XH-A_1x02_P2.50mm_Vertical
J7: MODE SW; JST_XH_B2B-XH-A_1x02_P2.50mm_Vertical
LED1: green ON; LED_D5.0mm
LED2: blue LINK; LED_D5.0mm
Q1: IRLB8748; TO-220-3_Vertical
R1, R2, R4, R5, R7, R8: 100k; R_Axial_DIN0207_L6.3mm_D2.5mm_P10.16mm_Horizontal
R3: 1R 5W; R_Axial_Power_L25.0mm_W9.0mm_P27.94mm
R6: 100R; R_Axial_DIN0207_L6.3mm_D2.5mm_P10.16mm_Horizontal
R9, R10: 330R; R_Axial_DIN0207_L6.3mm_D2.5mm_P10.16mm_Horizontal
U1: XIAO_ESP32S3+Wio-SX1262; XIAO_ESP32S3_Wio-SX1262_Socketed

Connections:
/ARM: J3.2, R3.1
/BAT_SW: C1.1, J4.2, J5.2, R1.1
/BUTTON: J6.1, U1.3 (D2)
/BUZZER: BZ1.1 (+), U1.2 (D1)
/CELL+: J2.2, J3.1, J4.1
/GATE: Q1.1 (G), R6.2, R7.1
/IGN+: J1.1, R3.2, R8.1
/IGN-: J1.2, Q1.2 (D), R4.1, R8.2
/LAUNCH_GATE: R6.1, U1.6 (D5)
/LED_LINK: R10.1, U1.7 (D6/TX)
/LED_LINK_A: LED2.2 (A), R10.2
/LED_ON: R9.1, U1.4 (D3)
/LED_ON_A: LED1.2 (A), R9.2
/MODE: J7.1, U1.8 (D7/RX)
/SENSE_BAT: R1.2, R2.1, U1.1 (D0/A0)
/SENSE_LAUNCH: R4.2, R5.1, U1.5 (D4/A4)
GND: BZ1.2 (-), C1.2, J2.1, J5.1, J6.2, J7.2, LED1.1 (K), LED2.1 (K), Q1.3 (S), R2.2, R5.2, R7.2, U1.13 (GND)

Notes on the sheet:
Ground station: XIAO ESP32-S3 + Wio-SX1262
Plugged into two 1x7 female headers. Pins: pins::ground in include/board_pins.h
Circuits explained in docs/HARDWARE.md (Ground station)
Power: 18650 on J2, power switch SW1 on J4, XIAO BAT pads on J5
CELL+ is before the power switch (launch channel). BAT_SW feeds the XIAO BAT+ pad.
Launch channel
CELL+ -> ARM switch SW2 (J3) -> R3 1 ohm 5 W -> igniter (J1) -> Q1 drain; source -> cell -
SENSE_LAUNCH: 0 V = ARM off; ~2/3 battery = armed, no igniter (R8); ~battery = igniter
Panel
Button S1 (J6) and MODE switch SW3 (J7) to GND, internal pull-ups; open MODE = BENCH
M3 mounting holes

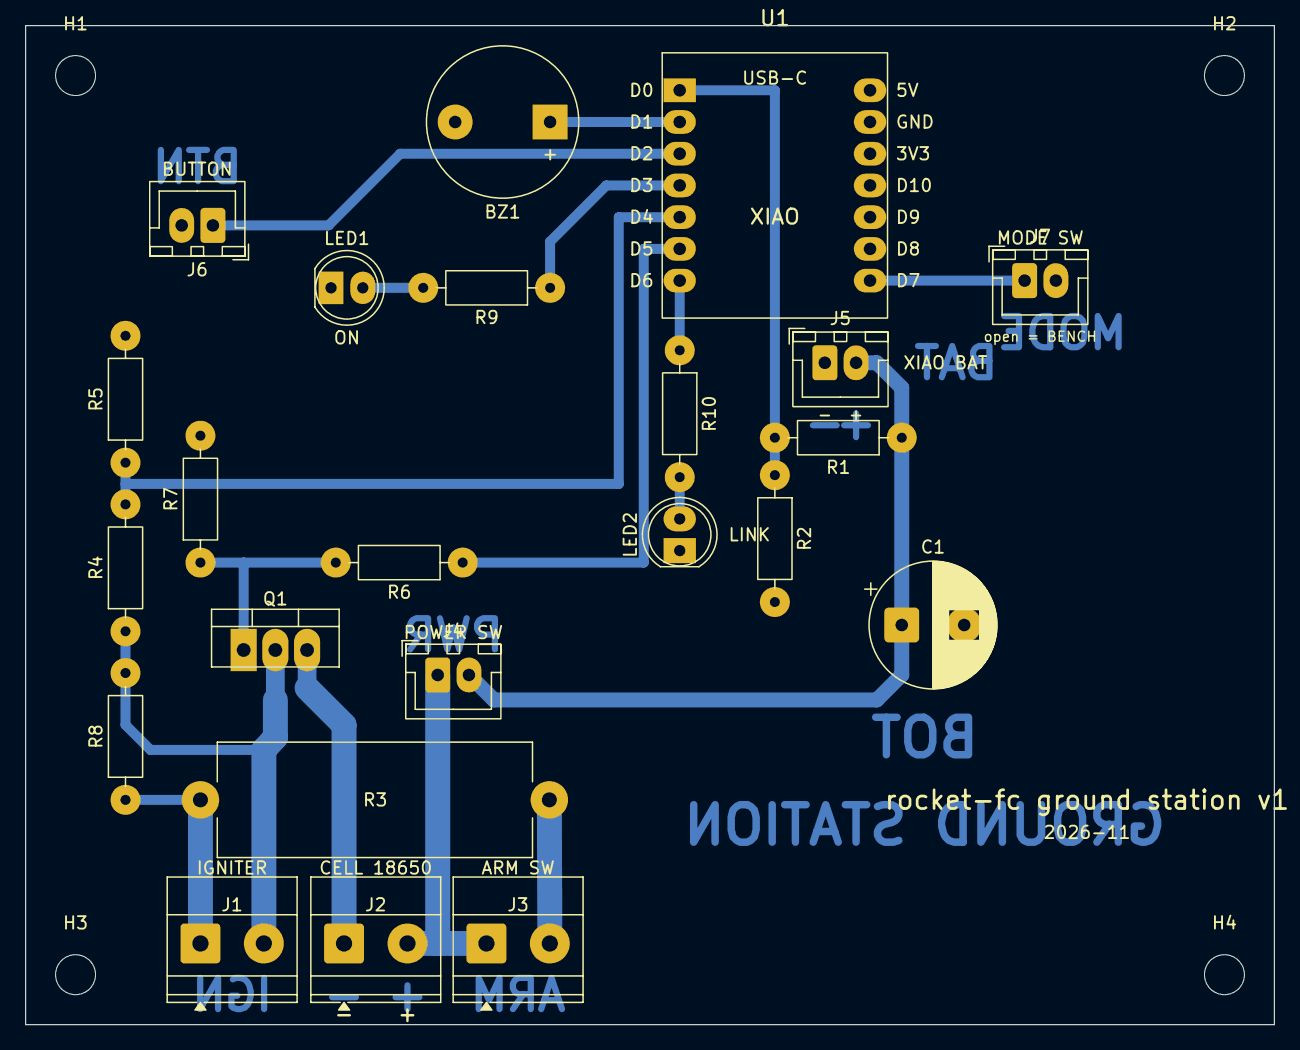
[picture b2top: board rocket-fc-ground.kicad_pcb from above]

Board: 2 copper layers, 100.0 x 80.0 mm, 27 parts (0 on the bottom side), 17 nets.
